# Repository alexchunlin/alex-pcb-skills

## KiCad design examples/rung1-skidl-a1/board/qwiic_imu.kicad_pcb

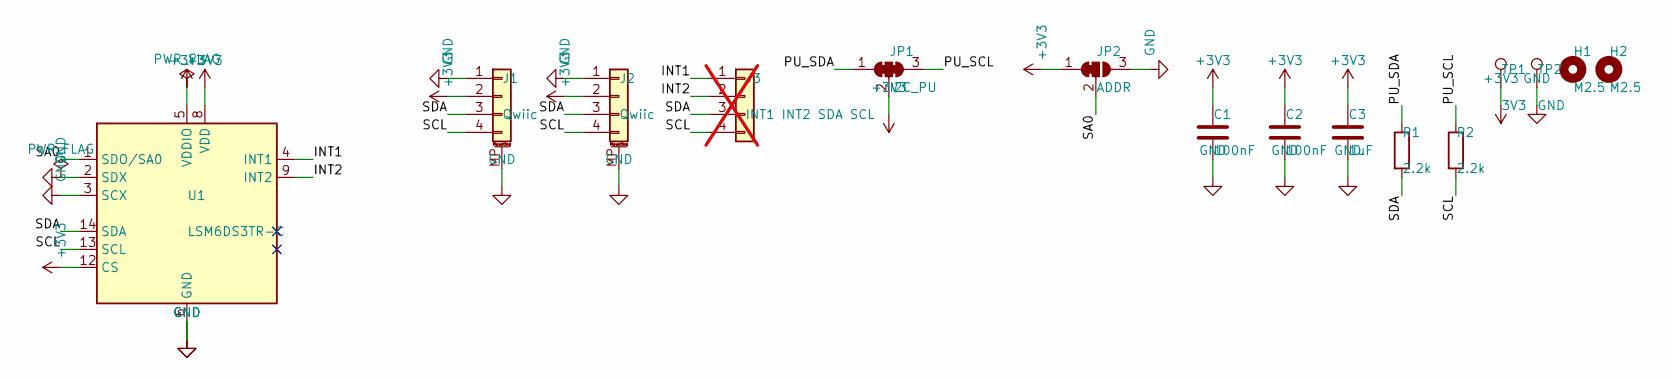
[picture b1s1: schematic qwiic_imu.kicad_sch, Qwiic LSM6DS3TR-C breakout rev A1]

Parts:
C1, C2: 100nF; C_0603_1608Metric; MPN CC0603KRX7R9BB104; LCSC C14663
C3: 1uF; C_0603_1608Metric; MPN CL10A105KB8NNNC; LCSC C15849
H1, H2: M2.5; MountingHole_2.7mm_M2.5; MPN mounting hole
J1, J2: Qwiic; JST_SH_SM04B-SRSS-TB_1x04-1MP_P1.00mm_Horizontal; MPN SM04B-SRSS-TB(LF)(SN); LCSC C160404
J3: INT1 INT2 SDA SCL; PinHeader_1x04_P2.54mm_Vertical; MPN PinHeader 1x4 2.54mm; not fitted
JP1: I2C_PU; SolderJumper-3_P1.3mm_Bridged123_RoundedPad1.0x1.5mm; MPN solder jumper
JP2: ADDR; SolderJumper-3_P1.3mm_Bridged12_RoundedPad1.0x1.5mm; MPN solder jumper
R1, R2: 2.2k; R_0603_1608Metric; MPN 0603WAF2201T5E; LCSC C4190
TP1: 3V3; TestPoint_Pad_1.5x1.5mm_Silk0.2; MPN test pad
TP2: GND; TestPoint_Pad_1.5x1.5mm_Silk0.2; MPN test pad
U1: LSM6DS3TR-C; LGA-14_3x2.5mm_P0.5mm_LayoutBorder3x4y; MPN LSM6DS3TR-C; LCSC C967633

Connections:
+3V3: C1.1, C2.1, C3.1, J1.2, J2.2, JP1.2 (C), JP2.1 (A), TP1.1, U1.5 (VDDIO), U1.8 (VDD), U1.12 (CS)
/INT1: J3.1, U1.4 (INT1)
/INT2: J3.2, U1.9 (INT2)
/PU_SCL: JP1.3 (B), R2.1
/PU_SDA: JP1.1 (A), R1.1
/SA0: JP2.2 (C), U1.1 (SDO/SA0)
/SCL: J1.4, J2.4, J3.4, R2.2, U1.13 (SCL)
/SDA: J1.3, J2.3, J3.3, R1.2, U1.14 (SDA)
GND: C1.2, C2.2, C3.2, J1.1, J1.MP (MountPin), J2.1, J2.MP (MountPin), JP2.3 (B), TP2.1, U1.2 (SDX), U1.3 (SCX), U1.6 (GND), U1.7 (GND)

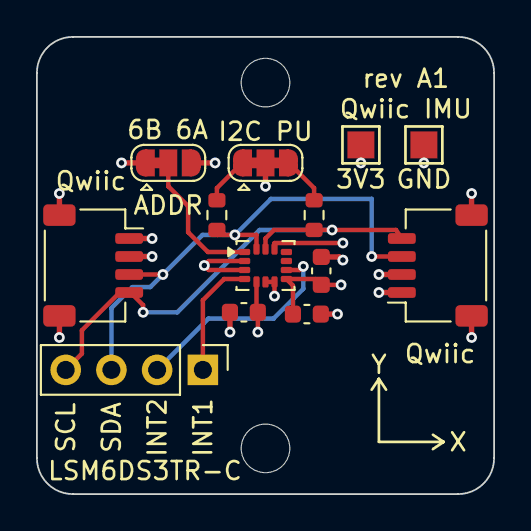
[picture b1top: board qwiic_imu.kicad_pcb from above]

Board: 4 copper layers, 25.4 x 25.4 mm, 15 parts (0 on the bottom side), 9 nets.

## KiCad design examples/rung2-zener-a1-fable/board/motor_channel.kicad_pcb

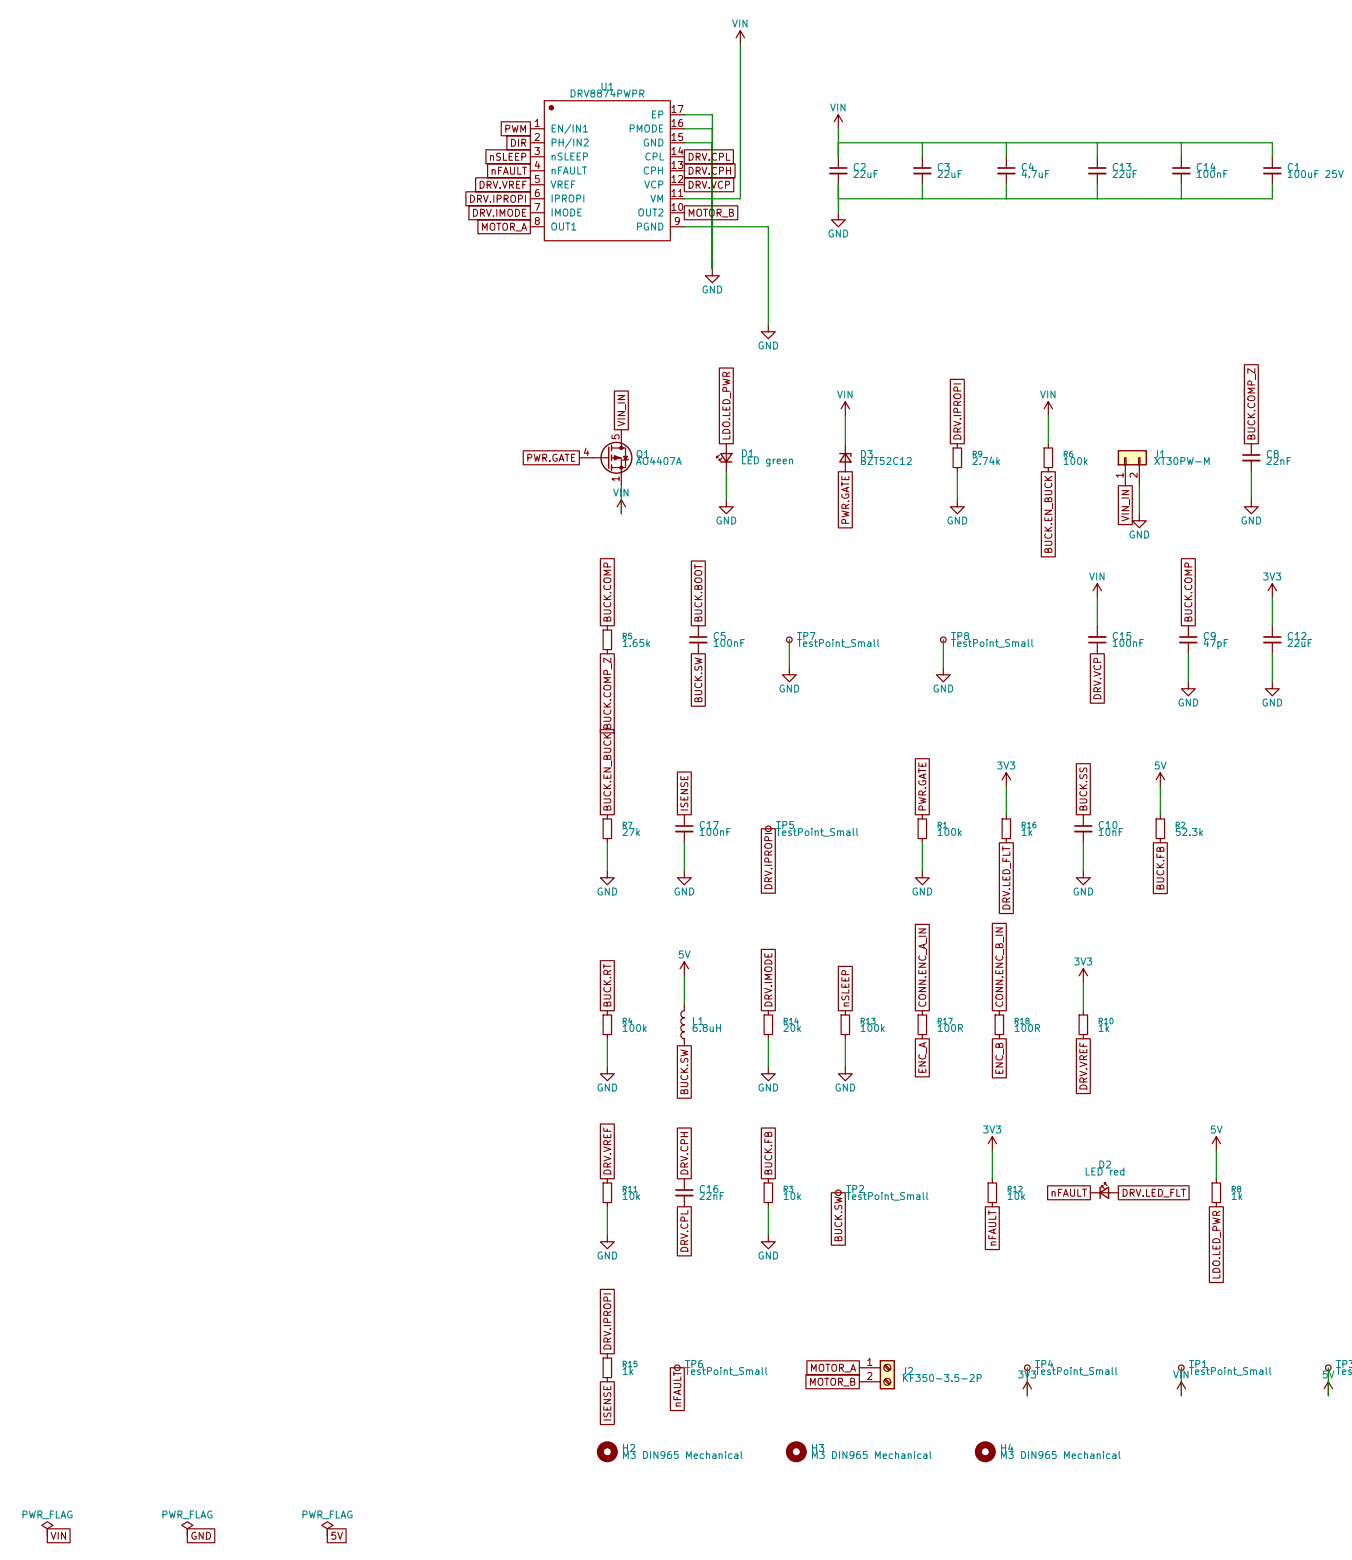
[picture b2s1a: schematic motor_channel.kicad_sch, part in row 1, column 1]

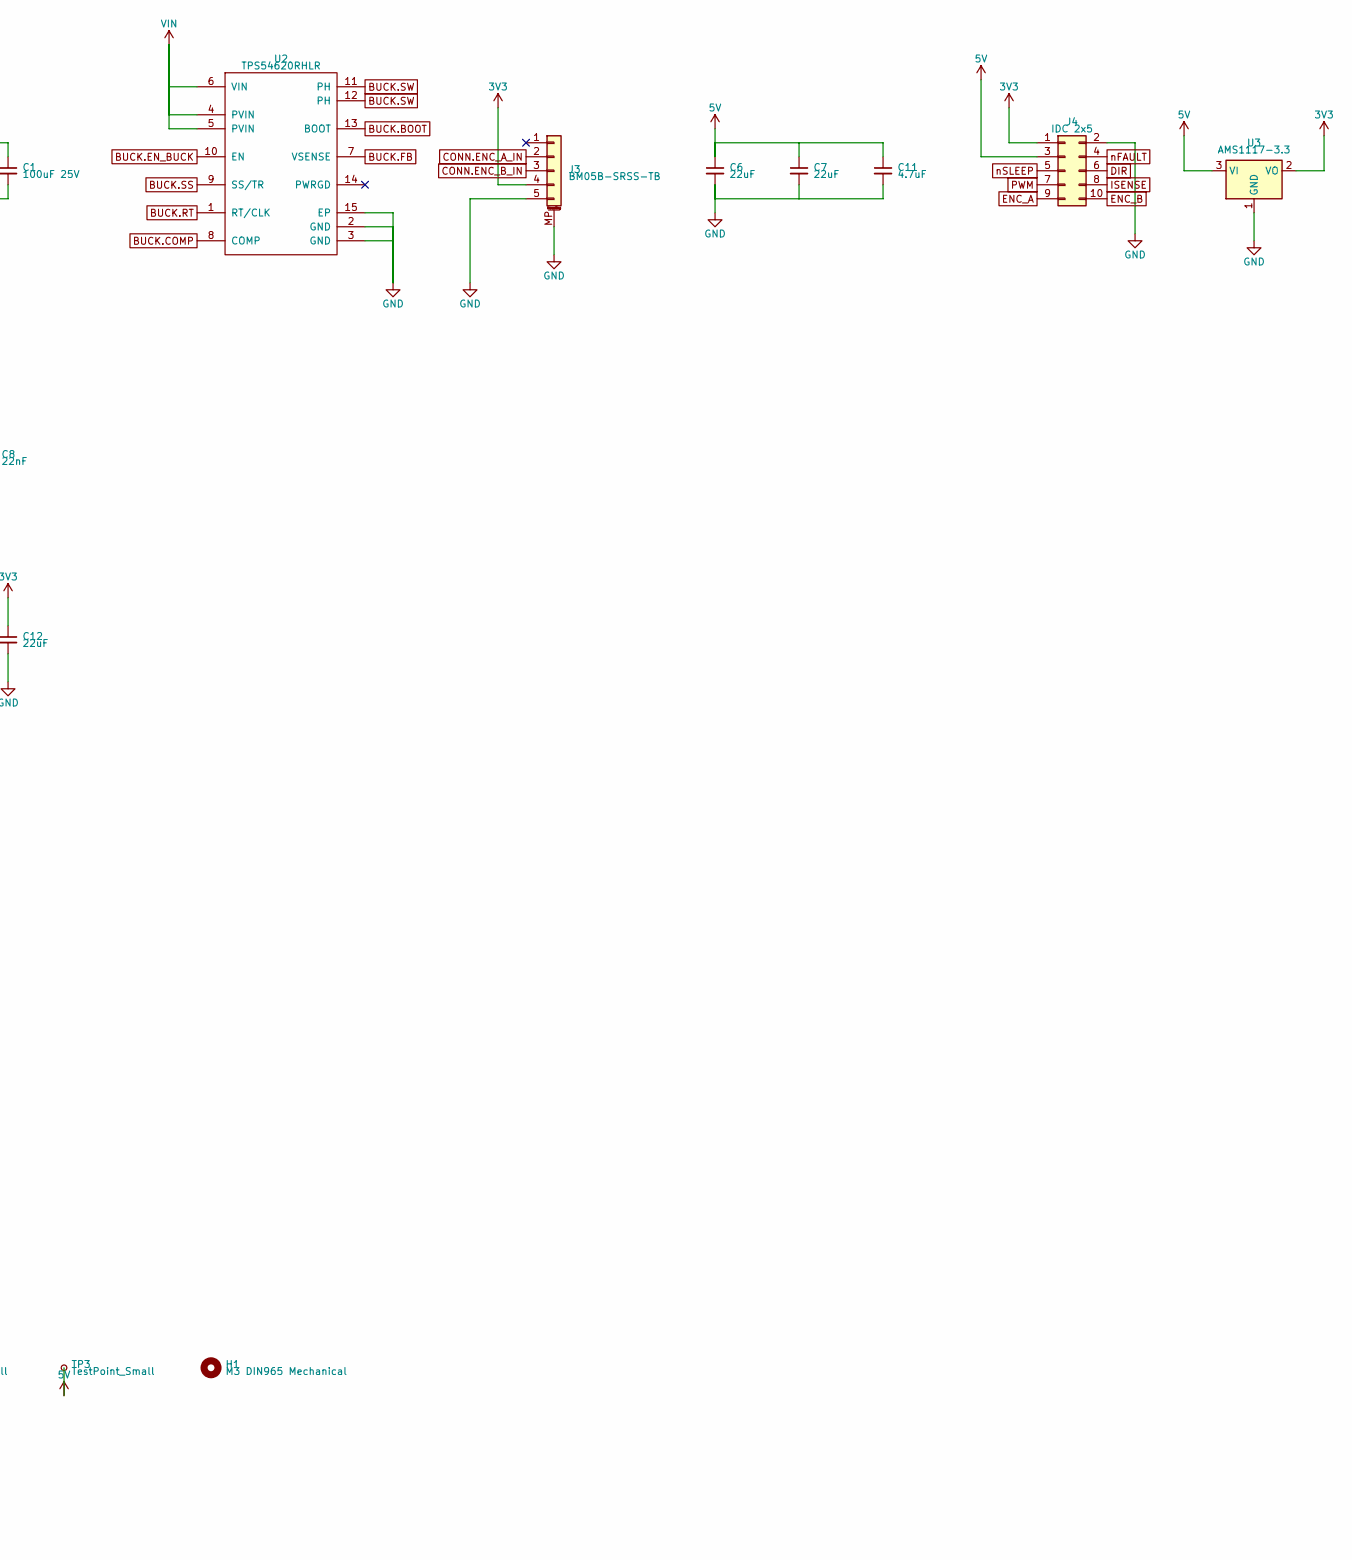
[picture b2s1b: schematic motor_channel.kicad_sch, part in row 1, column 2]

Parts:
C1: 100uF 25V; CP_Elec_6.3x7.7; MPN RVT100UF25V67RV0011; LCSC C2836443
C2, C3, C13: 22uF; C_1206_3216Metric; MPN CL31A226KAHNNNE; LCSC C12891
C4, C11: 4.7uF; C_0603_1608Metric; MPN CL10A475KA8NQNC; LCSC C69335
C5, C14, C15, C17: 100nF; C_0402_1005Metric; MPN CL05B104KB54PNC; LCSC C307331
C6, C7, C12: 22uF; C_0805_2012Metric; MPN CL21A226MPQNNNE; LCSC C29277
C8, C16: 22nF; C_0402_1005Metric; MPN 0402B223K500NT; LCSC C1532
C9: 47pF; C_0402_1005Metric; MPN 0402CG470J500NT; LCSC C1567
C10: 10nF; C_0402_1005Metric; MPN CL05B103KB5NNNC; LCSC C15195
D1: LED green; LED_0603_1608Metric; MPN KT-0603G; LCSC C12624
D2: LED red; LED_0603_1608Metric; MPN KT-0603R; LCSC C2286
D3: BZT52C12; D_SOD-123; MPN BZT52C12; LCSC C43491
H1, H2, H3, H4: M3 DIN965 Mechanical; MountingHole_3.2mm_M3_DIN965
J1: XT30PW-M; AMASS_XT30PW-M_1x02_P2.50mm_Horizontal; MPN XT30PW-M; LCSC C431092
J2: KF350-3.5-2P; TerminalBlock_PT-1.5-2-3.5-H_1x02_P3.50mm_Horizontal; MPN KF350-3.5-2P; LCSC C474892
J3: BM05B-SRSS-TB; JST_SH_BM05B-SRSS-TB_1x05-1MP_P1.00mm_Vertical; MPN BM05B-SRSS-TB(LF)(SN); LCSC C160391
J4: IDC 2x5; IDC-Header_2x05_P2.54mm_Vertical; MPN IDC2.54-2*5PZ; LCSC C53207560
L1: 6.8uH; L_8.0x8.0_H4.0; MPN FXL0840-6R8-M; LCSC C5359253
Q1: AO4407A; SOIC-8_3.9x4.9mm_P1.27mm; MPN AO4407A; LCSC C16072
R1, R4, R6, R13: 100k; R_0402_1005Metric; MPN 0402WGF1003TCE; LCSC C25741
R2: 52.3k; R_0402_1005Metric; MPN 0402WGF5232TCE; LCSC C26982
R3, R11, R12: 10k; R_0402_1005Metric; MPN 0402WGF1002TCE; LCSC C25744
R5: 1.65k; R_0402_1005Metric; MPN 0402WGF1651TCE; LCSC C25869
R7: 27k; R_0402_1005Metric; MPN 0402WGF2702TCE; LCSC C25771
R8, R10, R15, R16: 1k; R_0402_1005Metric; MPN 0402WGF1001TCE; LCSC C11702
R9: 2.74k; R_0402_1005Metric; MPN 0402WGF2741TCE; LCSC C33360
R14: 20k; R_0402_1005Metric; MPN 0402WGF2002TCE; LCSC C25765
R17, R18: 100R; R_0402_1005Metric; MPN 0402WGF1000TCE; LCSC C25076
TP1, TP2, TP3, TP4, TP5, TP6, TP7, TP8: TestPoint_Small; TestPoint_Pad_1.5x1.5mm
U1: DRV8874PWPR; HTSSOP-16_L5.0-W4.4-P0.65-LS6.4-BL-EP; MPN DRV8874PWPR; LCSC C1855818
U2: TPS54620RHLR; VQFN-14_L3.5-W3.5-P0.50-TL-EP_TPS54622RHLT; MPN TPS54620RHLR; LCSC C263274
U3: AMS1117-3.3; SOT-223-3_TabPin2; MPN AMS1117-3.3; LCSC C6186

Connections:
3V3: C12.1, J3.4, J4.1, R10.1, R12.1, R16.1, TP4.1, U3.2 (VO)
5V: C6.1, C7.1, C11.1, J4.3, L1.2, R2.1, R8.1, TP3.1, U3.3 (VI)
BUCK.BOOT: C5.1, U2.13 (BOOT)
BUCK.COMP: C9.1, R5.1, U2.8 (COMP)
BUCK.COMP_Z: C8.1, R5.2
BUCK.EN_BUCK: R6.2, R7.1, U2.10 (EN)
BUCK.FB: R2.2, R3.1, U2.7 (VSENSE)
BUCK.RT: R4.1, U2.1 (RT/CLK)
BUCK.SS: C10.1, U2.9 (SS/TR)
BUCK.SW: C5.2, L1.1, TP2.1, U2.11 (PH), U2.12 (PH)
BUCK.U2.NC_U_PWRGD: U2.14 (PWRGD)
CONN.ENC_A_IN: J3.2, R17.1
CONN.ENC_B_IN: J3.3, R18.1
CONN.J3.NC_J_Pin_1: J3.1
DIR: J4.6, U1.2 (PH/IN2)
DRV.CPH: C16.1, U1.13 (CPH)
DRV.CPL: C16.2, U1.14 (CPL)
DRV.IMODE: R14.1, U1.7 (IMODE)
DRV.IPROPI: R9.1, R15.1, TP5.1, U1.6 (IPROPI)
DRV.LED_FLT: D2.2 (A), R16.2
DRV.VCP: C15.1, U1.12 (VCP)
DRV.VREF: R10.2, R11.1, U1.5 (VREF)
ENC_A: J4.9, R17.2
ENC_B: J4.10, R18.2
GND: C1.2, C2.2, C3.2, C4.2, C6.2, C7.2, C8.2, C9.2, C10.2, C11.2, C12.2, C13.2, C14.2, C17.2, D1.1 (K), J1.2, J3.5, J3.MP (MountPin), J4.2, R1.2, R3.2, R4.2, R7.2, R9.2, R11.2, R13.2, R14.2, TP7.1, TP8.1, U1.9 (PGND), U1.15 (GND), U1.16 (PMODE), U1.17 (EP), U2.2 (GND), U2.3 (GND), U2.15 (EP), U3.1 (GND)
ISENSE: C17.1, J4.8, R15.2
LDO.LED_PWR: D1.2 (A), R8.2
MOTOR_A: J2.1, U1.8 (OUT1)
MOTOR_B: J2.2, U1.10 (OUT2)
PWM: J4.7, U1.1 (EN/IN1)
PWR.GATE: D3.2 (A), Q1.4 (G), R1.1
VIN: C1.1, C2.1, C3.1, C4.1, C13.1, C14.1, C15.2, D3.1 (K), Q1.1 (S), Q1.2 (S), Q1.3 (S), R6.1, TP1.1, U1.11 (VM), U2.4 (PVIN), U2.5 (PVIN), U2.6 (VIN)
VIN_IN: J1.1, Q1.5 (D), Q1.6 (D), Q1.7 (D), Q1.8 (D)
nFAULT: D2.1 (K), J4.4, R12.2, TP6.1, U1.4 (nFAULT)
nSLEEP: J4.5, R13.1, U1.3 (nSLEEP)

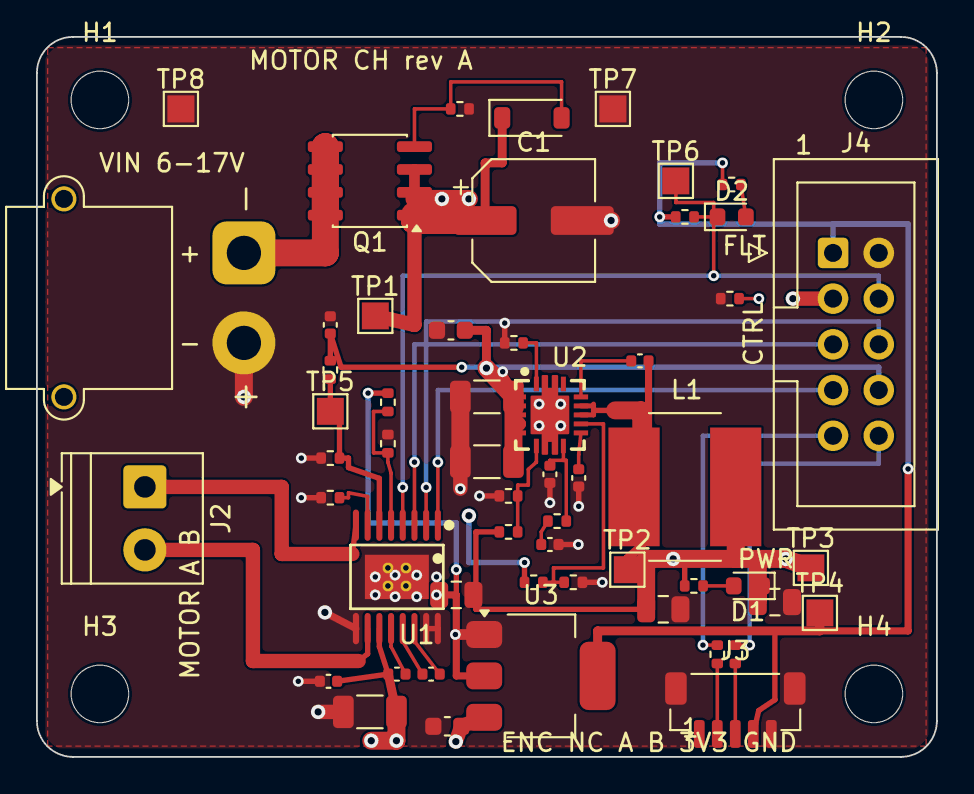
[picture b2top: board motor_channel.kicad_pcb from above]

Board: 4 copper layers, 50.0 x 40.0 mm, 59 parts (0 on the bottom side), 33 nets.
